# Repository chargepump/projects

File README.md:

# projects
My project repository

kbalaji, b.e.
embedded systems design & development

this folder contains miscellaneous projects that i am working on

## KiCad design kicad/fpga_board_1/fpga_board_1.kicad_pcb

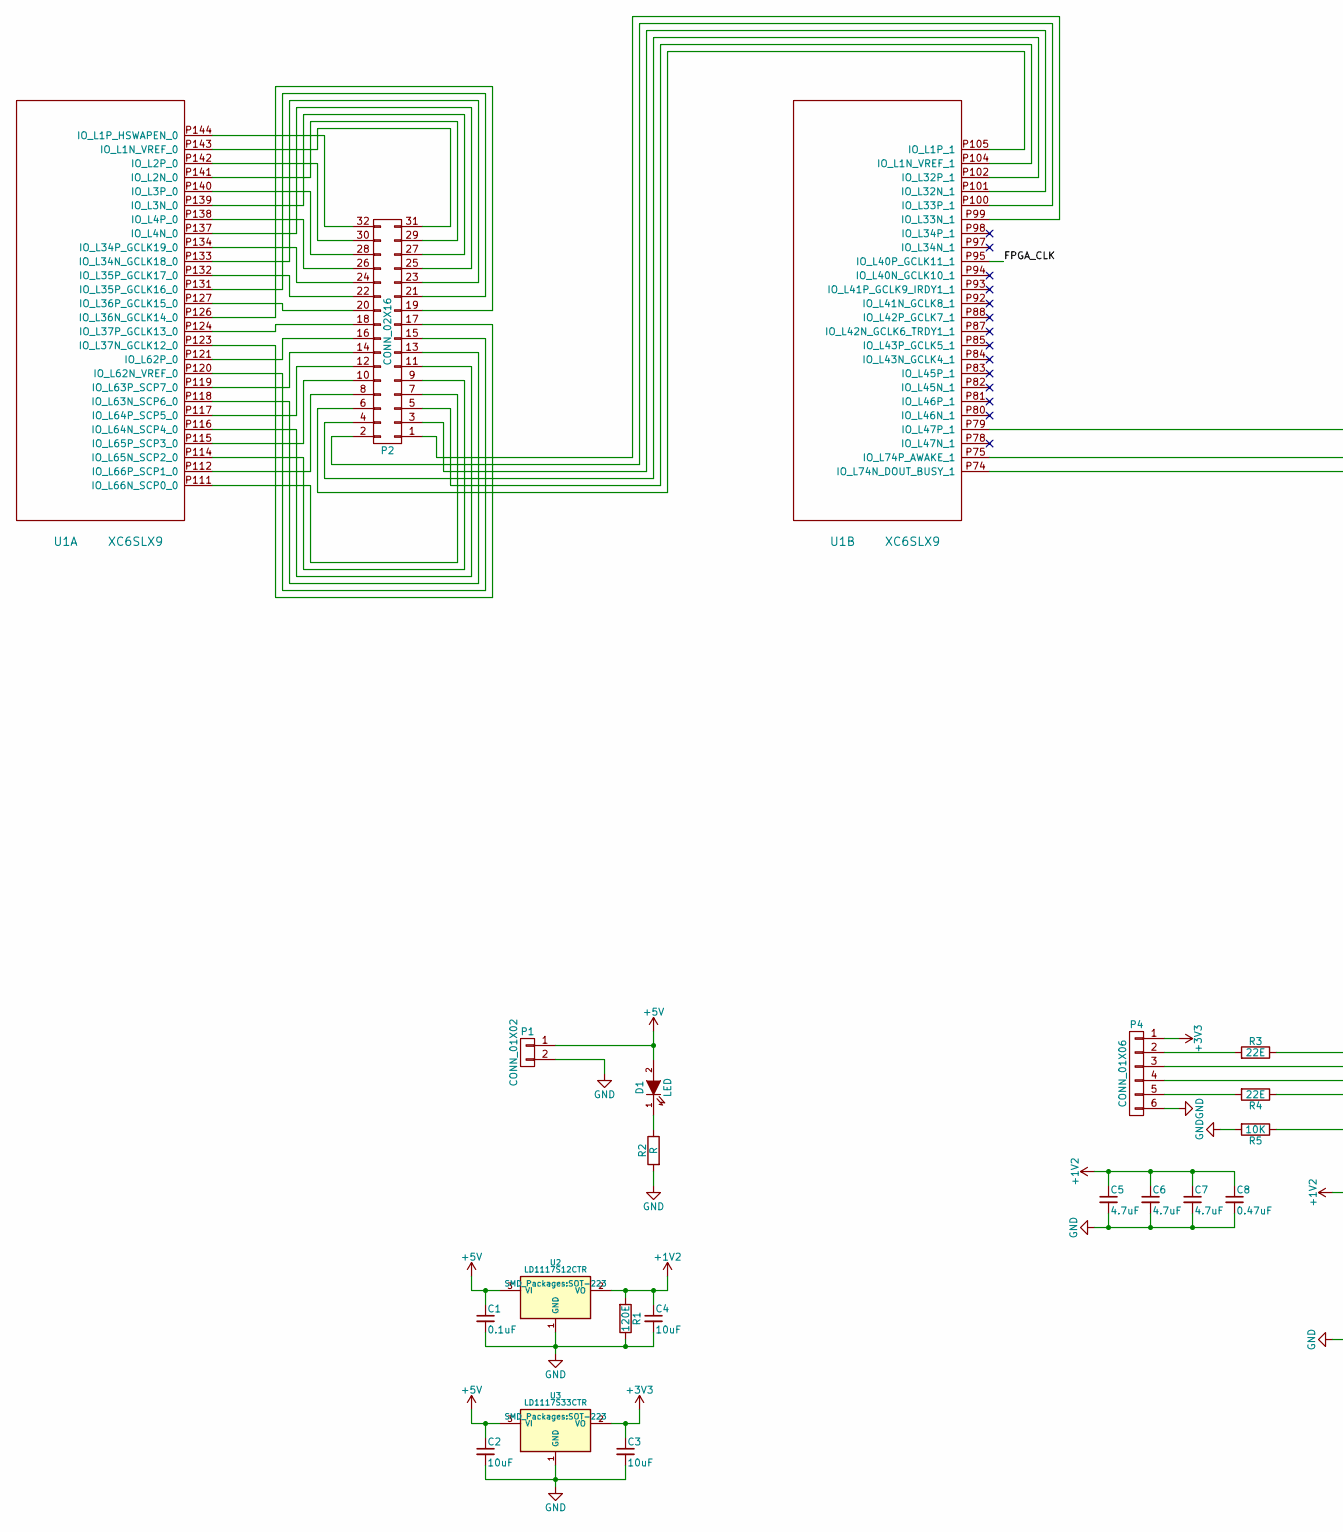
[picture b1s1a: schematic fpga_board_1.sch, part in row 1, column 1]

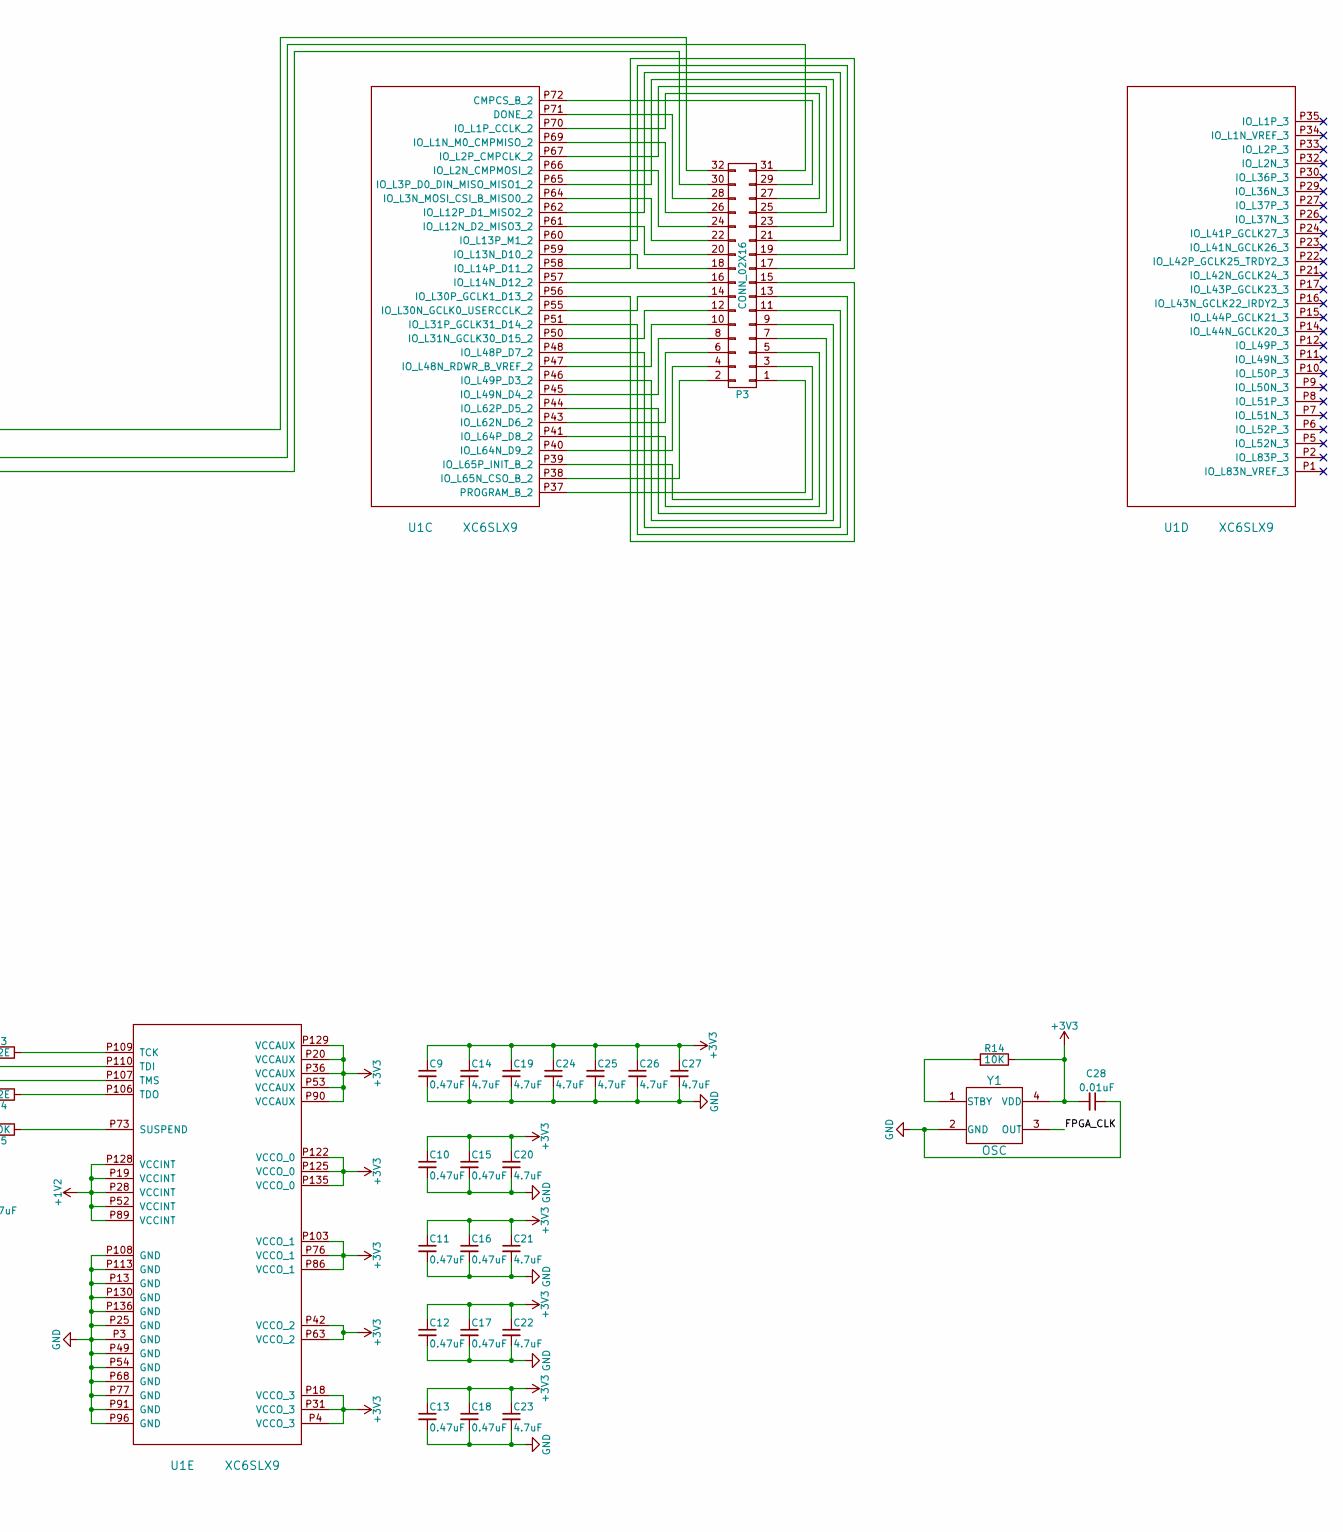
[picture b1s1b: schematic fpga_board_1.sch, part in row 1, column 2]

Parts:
C1: 0.1uF; C_0603_HandSoldering
C2, C3, C4: 10uF; C_0603_HandSoldering
C5, C6, C7, C14, C19, C20, C21, C22, C23, C24, C25, C26, C27: 4.7uF; C_0805_HandSoldering
C8, C9, C10, C11, C12, C13, C15, C16, C17, C18: 0.47uF; C_0402
C28: 0.01uF; C_0603_HandSoldering
D1: LED; LED-0805
P1: CONN_01X02; Pin_Header_Straight_1x02
P2, P3: CONN_02X16; Pin_Header_Straight_2x16
P4: CONN_01X06; Pin_Header_Straight_1x06
R1: 120E; R_0603_HandSoldering
R2: R; R_0603_HandSoldering
R3, R4: 22E; R_0603_HandSoldering
R5, R14: 10K; R_0603_HandSoldering
U1: XC6SLX9; SMD_TQFP_144_
U2: LD1117S12CTR; SOT-223
U3: LD1117S33CTR; SOT-223
Y1: OSC; OSC_SMD_QFN_5x3.2mm

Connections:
+1V2: C4.1, C5.1, C6.1, C7.1, C8.1, R1.2, U1.P19 (VCCINT), U1.P28 (VCCINT), U1.P52 (VCCINT), U1.P89 (VCCINT), U1.P128 (VCCINT), U2.2 (VO), U2.4
+3V3: C3.1, C9.1, C10.1, C11.1, C12.1, C13.1, C14.1, C15.1, C16.1, C17.1, C18.1, C19.1, C20.1, C21.1, C22.1, C23.1, C24.1, C25.1, C26.1, C27.1, C28.2, P4.1, R14.1, U1.P4 (VCCO_3), U1.P18 (VCCO_3), U1.P20 (VCCAUX), U1.P31 (VCCO_3), U1.P36 (VCCAUX), U1.P42 (VCCO_2), U1.P53 (VCCAUX), U1.P63 (VCCO_2), U1.P76 (VCCO_1), U1.P86 (VCCO_1), U1.P90 (VCCAUX), U1.P103 (VCCO_1), U1.P122 (VCCO_0), U1.P125 (VCCO_0), U1.P129 (VCCAUX), U1.P135 (VCCO_0), U3.2 (VO), U3.4, Y1.4 (VDD)
+5V: C1.1, C2.1, D1.2 (A), P1.1, U2.3 (VI), U3.3 (VI)
/FPGA_CLK: U1.P95 (IO_L40P_GCLK11_1), Y1.3 (OUT)
GND: C1.2, C2.2, C3.2, C4.2, C5.2, C6.2, C7.2, C8.2, C9.2, C10.2, C11.2, C12.2, C13.2, C14.2, C15.2, C16.2, C17.2, C18.2, C19.2, C20.2, C21.2, C22.2, C23.2, C24.2, C25.2, C26.2, C27.2, C28.1, P1.2, P4.6, R1.1, R2.2, R5.2, U1.P3 (GND), U1.P13 (GND), U1.P25 (GND), U1.P49 (GND), U1.P54 (GND), U1.P68 (GND), U1.P77 (GND), U1.P91 (GND), U1.P96 (GND), U1.P108 (GND), U1.P113 (GND), U1.P130 (GND), U1.P136 (GND), U2.1 (GND), U3.1 (GND), Y1.2 (GND)
unnamed: D1.1 (K), R2.1
unnamed: P2.1, U1.P99 (IO_L33N_1)
unnamed: P2.2, U1.P100 (IO_L33P_1)
unnamed: P2.3, U1.P101 (IO_L32N_1)
unnamed: P2.4, U1.P102 (IO_L32P_1)
unnamed: P2.5, U1.P104 (IO_L1N_VREF_1)
unnamed: P2.6, U1.P105 (IO_L1P_1)
unnamed: P2.7, U1.P111 (IO_L66N_SCP0_0)
unnamed: P2.8, U1.P112 (IO_L66P_SCP1_0)
unnamed: P2.9, U1.P114 (IO_L65N_SCP2_0)
unnamed: P2.10, U1.P115 (IO_L65P_SCP3_0)
unnamed: P2.11, U1.P116 (IO_L64N_SCP4_0)
unnamed: P2.12, U1.P117 (IO_L64P_SCP5_0)
unnamed: P2.13, U1.P118 (IO_L63N_SCP6_0)
unnamed: P2.14, U1.P119 (IO_L63P_SCP7_0)
unnamed: P2.15, U1.P120 (IO_L62N_VREF_0)
unnamed: P2.16, U1.P121 (IO_L62P_0)
unnamed: P2.17, U1.P123 (IO_L37N_GCLK12_0)
unnamed: P2.18, U1.P124 (IO_L37P_GCLK13_0)
unnamed: P2.19, U1.P126 (IO_L36N_GCLK14_0)
unnamed: P2.20, U1.P127 (IO_L36P_GCLK15_0)
unnamed: P2.21, U1.P131 (IO_L35P_GCLK16_0)
unnamed: P2.22, U1.P132 (IO_L35P_GCLK17_0)
unnamed: P2.23, U1.P133 (IO_L34N_GCLK18_0)
unnamed: P2.24, U1.P134 (IO_L34P_GCLK19_0)
unnamed: P2.25, U1.P137 (IO_L4N_0)
unnamed: P2.26, U1.P138 (IO_L4P_0)
unnamed: P2.27, U1.P139 (IO_L3N_0)
unnamed: P2.28, U1.P140 (IO_L3P_0)
unnamed: P2.29, U1.P141 (IO_L2N_0)
unnamed: P2.30, U1.P142 (IO_L2P_0)
unnamed: P2.31, U1.P143 (IO_L1N_VREF_0)
unnamed: P2.32, U1.P144 (IO_L1P_HSWAPEN_0)
unnamed: P3.1, U1.P37 (PROGRAM_B_2)
unnamed: P3.2, U1.P38 (IO_L65N_CSO_B_2)
unnamed: P3.3, U1.P39 (IO_L65P_INIT_B_2)
unnamed: P3.4, U1.P40 (IO_L64N_D9_2)
unnamed: P3.5, U1.P41 (IO_L64P_D8_2)
unnamed: P3.6, U1.P43 (IO_L62N_D6_2)
unnamed: P3.7, U1.P44 (IO_L62P_D5_2)
unnamed: P3.8, U1.P45 (IO_L49N_D4_2)
unnamed: P3.9, U1.P46 (IO_L49P_D3_2)
unnamed: P3.10, U1.P47 (IO_L48N_RDWR_B_VREF_2)
unnamed: P3.11, U1.P48 (IO_L48P_D7_2)
unnamed: P3.12, U1.P50 (IO_L31N_GCLK30_D15_2)
unnamed: P3.13, U1.P51 (IO_L31P_GCLK31_D14_2)
unnamed: P3.14, U1.P55 (IO_L30N_GCLK0_USERCCLK_2)
unnamed: P3.15, U1.P56 (IO_L30P_GCLK1_D13_2)
unnamed: P3.16, U1.P57 (IO_L14N_D12_2)
unnamed: P3.17, U1.P58 (IO_L14P_D11_2)
unnamed: P3.18, U1.P59 (IO_L13N_D10_2)
unnamed: P3.19, U1.P60 (IO_L13P_M1_2)
unnamed: P3.20, U1.P61 (IO_L12N_D2_MISO3_2)
unnamed: P3.21, U1.P62 (IO_L12P_D1_MISO2_2)
unnamed: P3.22, U1.P64 (IO_L3N_MOSI_CSI_B_MISO0_2)
unnamed: P3.23, U1.P65 (IO_L3P_D0_DIN_MISO_MISO1_2)
unnamed: P3.24, U1.P66 (IO_L2N_CMPMOSI_2)
unnamed: P3.25, U1.P67 (IO_L2P_CMPCLK_2)
unnamed: P3.26, U1.P69 (IO_L1N_M0_CMPMISO_2)
unnamed: P3.27, U1.P70 (IO_L1P_CCLK_2)
unnamed: P3.28, U1.P71 (DONE_2)
unnamed: P3.29, U1.P72 (CMPCS_B_2)
unnamed: P3.30, U1.P74 (IO_L74N_DOUT_BUSY_1)
unnamed: P3.31, U1.P75 (IO_L74P_AWAKE_1)
unnamed: P3.32, U1.P79 (IO_L47P_1)
unnamed: P4.2, R3.2
unnamed: P4.3, U1.P110 (TDI)
unnamed: P4.4, U1.P107 (TMS)
unnamed: P4.5, R4.2
unnamed: R3.1, U1.P109 (TCK)
unnamed: R4.1, U1.P106 (TDO)
unnamed: R5.1, U1.P73 (SUSPEND)
unnamed: R14.2, Y1.1 (STBY)

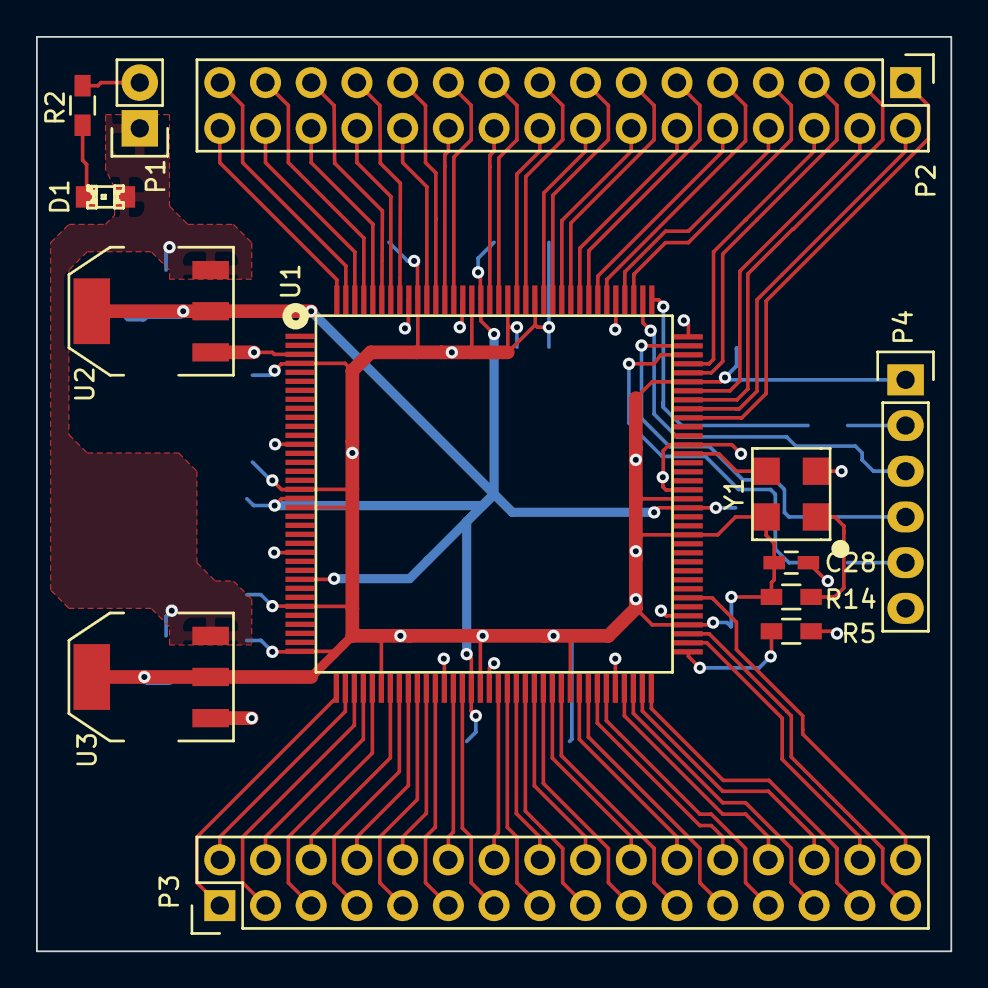
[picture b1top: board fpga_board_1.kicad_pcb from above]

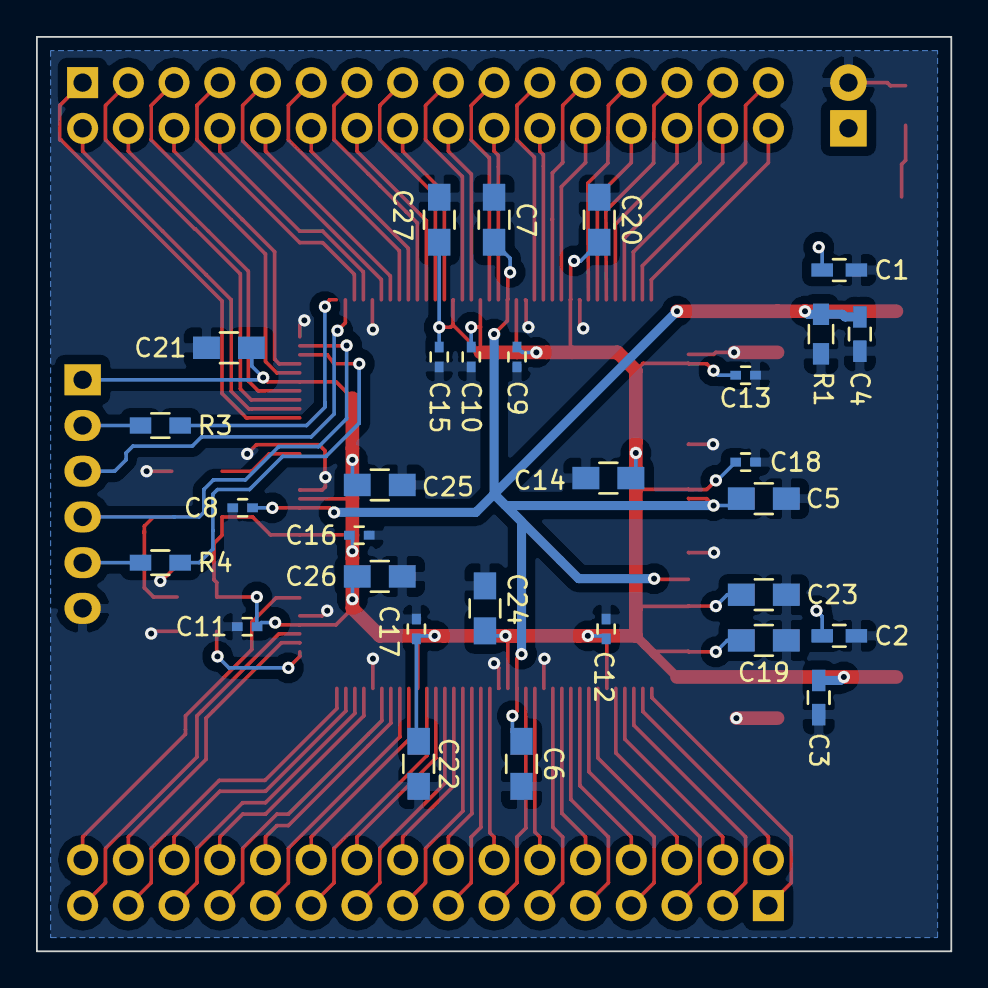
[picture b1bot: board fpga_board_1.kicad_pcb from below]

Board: 2 copper layers, 50.8 x 50.8 mm, 43 parts (30 on the bottom side), 78 nets.

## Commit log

2015-07-30 Uploaded two kicad designs; one, a Spartan 6 breakout board and another a RS232 transceiver.
2015-07-30 Trimming a few things ...
